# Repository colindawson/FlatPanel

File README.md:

# Remote FlatPanel to help with taking calibration frames.

This flat panel is going to be an open source, dimmable flat panel for astronomy.

## Features
- Dimmable flat panel
- Optional dew heater
- Flat panel acts like lens cap
- AsiAir remote controlable (both for heater and panel)
- oLed display for local control
- Wifi remote control
- Ascom Alpaca control
- Temperature and humidity sensor
- Fully automatic mode for dew heater

Above is the fully list of features that I'm planning.  Some of the features will cancel out other features. For example Fully Automatic mode will be available for the dew heater, to use the minimum power so that it keeps away dew without human interaction, however I want to have the ability to overrride this in several ways - Using an output from the AsiAir, a dedicated web page, Ascom Alpaca or manually via the display.

The plan is that this is going to be a full solution for any size scope, however, my initial project is based on creating a Panel for my SpaceCat 51 Scope.   Once that is working, I'll be looking at how to modify the project to work with my Meade LX-90.

## Discord

[cjdSkunkWorks/FlatPanel](https://discord.com/channels/800391513091211284/1350925191181631498)

## Todo list
- ~~Upload Display board design prototype~~ (done)
- ~~Upload Mainboard design prototype~~ (done)
- Finish designing 3D files for the SpaceCat51
  
- Upload 3d models for the SpaceCat51
- Finalise PCB Layout for Display Board
- Finalise PCB Layout for Mainboard
- Figure out display controls for manual mode
- Create micropython source oode for Pico
- Upgrade MicroPython code to support Pico W, for Web access
- Upgrade MicroPyton code to implement ASCOM Alpaca support

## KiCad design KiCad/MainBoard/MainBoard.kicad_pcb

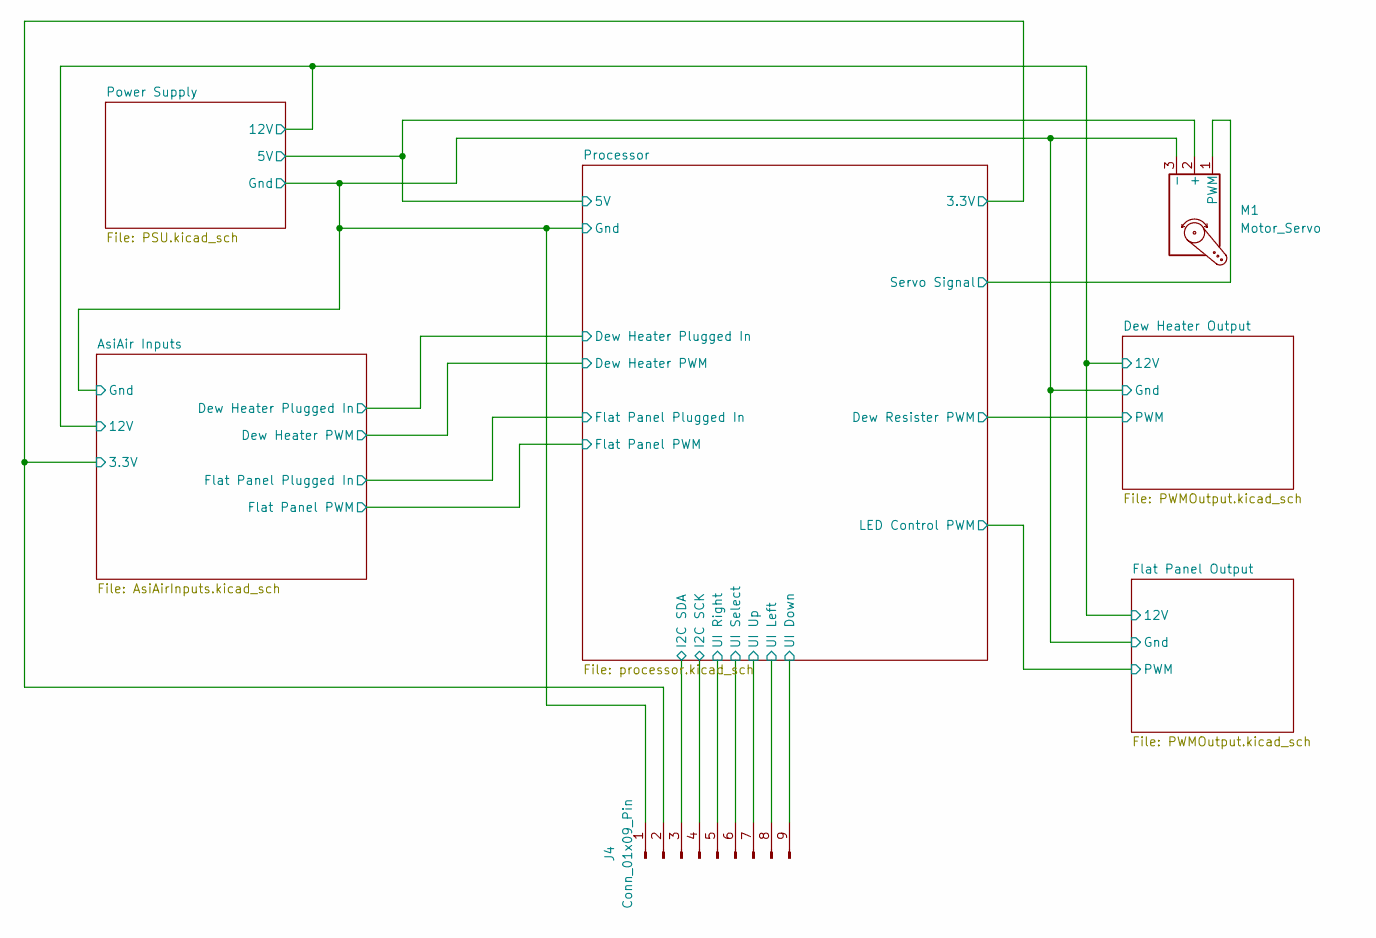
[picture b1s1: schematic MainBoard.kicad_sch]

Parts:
J4: Conn_01x09_Pin; PinHeader_2x05_P2.54mm_Horizontal
M1: Motor_Servo; PinHeader_1x03_P2.54mm_Vertical

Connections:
/AsiAir Inputs/3.3V: J4.2; also elsewhere on the board
/AsiAir Inputs/Gnd: J4.1, M1.3 (-); also elsewhere on the board
/Power Supply/5V: M1.2 (+); also elsewhere on the board
/Processor/I2C SCK: J4.4; also elsewhere on the board
/Processor/I2C SDA: J4.3; also elsewhere on the board
/Processor/Servo Signal: M1.1 (PWM); also elsewhere on the board
/Processor/UI Down: J4.9; also elsewhere on the board
/Processor/UI Left: J4.8; also elsewhere on the board
/Processor/UI Right: J4.5; also elsewhere on the board
/Processor/UI Select: J4.6; also elsewhere on the board
/Processor/UI Up: J4.7; also elsewhere on the board

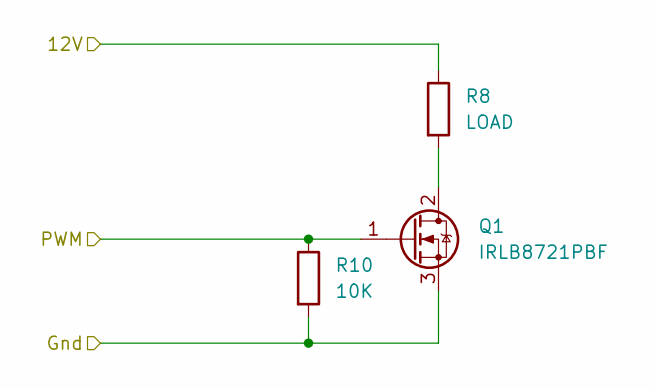
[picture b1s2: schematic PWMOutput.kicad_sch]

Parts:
Q1: IRLB8721PBF; TO-220-3_Vertical
R8: LOAD; JST_XH_B2B-XH-A_1x02_P2.50mm_Vertical
R10: 10K; R_Axial_DIN0204_L3.6mm_D1.6mm_P5.08mm_Horizontal

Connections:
/AsiAir Inputs/12V: R8.1; also elsewhere on the board
/AsiAir Inputs/Gnd: Q1.3 (S), R10.2; also elsewhere on the board
/Dew Heater Output/PWM: Q1.1 (G), R10.1; also elsewhere on the board
unnamed: Q1.2 (D), R8.2

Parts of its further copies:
Q2: IRLB8721PBF; TO-220-3_Vertical
R9: LOAD; JST_XH_B2B-XH-A_1x02_P2.50mm_Vertical
R11: 10K; R_Axial_DIN0204_L3.6mm_D1.6mm_P5.08mm_Horizontal

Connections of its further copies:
/AsiAir Inputs/12V: R9.1; also elsewhere on the board
/AsiAir Inputs/Gnd: Q2.3 (S), R11.2; also elsewhere on the board
/Flat Panel Output/PWM: Q2.1 (G), R11.1; also elsewhere on the board
unnamed: Q2.2 (D), R9.2

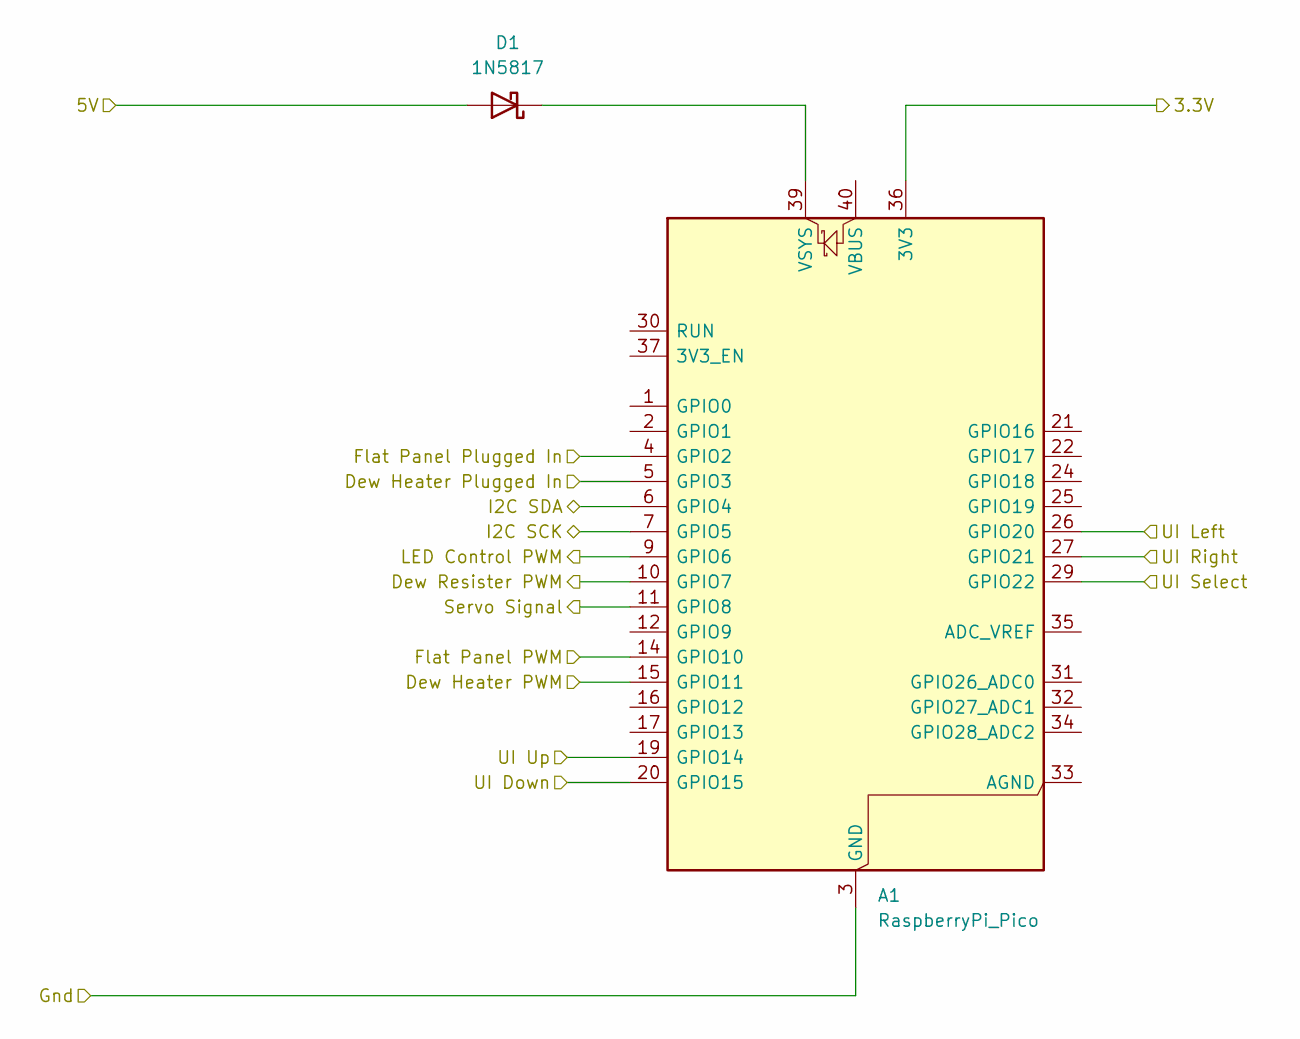
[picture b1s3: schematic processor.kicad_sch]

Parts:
A1: RaspberryPi_Pico; RaspberryPi_Pico_Common_Unspecified
D1: 1N5817; D_DO-15_P10.16mm_Horizontal

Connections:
/AsiAir Inputs/3.3V: A1.36 (3V3); also elsewhere on the board
/AsiAir Inputs/Dew Heater PWM: A1.15 (GPIO11); also elsewhere on the board
/AsiAir Inputs/Dew Heater Plugged In: A1.5 (GPIO3); also elsewhere on the board
/AsiAir Inputs/Flat Panel PWM: A1.14 (GPIO10); also elsewhere on the board
/AsiAir Inputs/Flat Panel Plugged In: A1.4 (GPIO2); also elsewhere on the board
/AsiAir Inputs/Gnd: A1.3 (GND), A1.8 (GND), A1.13 (GND), A1.18 (GND), A1.23 (GND), A1.28 (GND), A1.38 (GND); also elsewhere on the board
/Dew Heater Output/PWM: A1.10 (GPIO7); also elsewhere on the board
/Flat Panel Output/PWM: A1.9 (GPIO6); also elsewhere on the board
/Power Supply/5V: D1.2 (A); also elsewhere on the board
/Processor/I2C SCK: A1.7 (GPIO5); also elsewhere on the board
/Processor/I2C SDA: A1.6 (GPIO4); also elsewhere on the board
/Processor/Servo Signal: A1.11 (GPIO8); also elsewhere on the board
/Processor/UI Down: A1.20 (GPIO15); also elsewhere on the board
/Processor/UI Left: A1.26 (GPIO20); also elsewhere on the board
/Processor/UI Right: A1.27 (GPIO21); also elsewhere on the board
/Processor/UI Select: A1.29 (GPIO22); also elsewhere on the board
/Processor/UI Up: A1.19 (GPIO14); also elsewhere on the board
unnamed: A1.39 (VSYS), D1.1 (K)

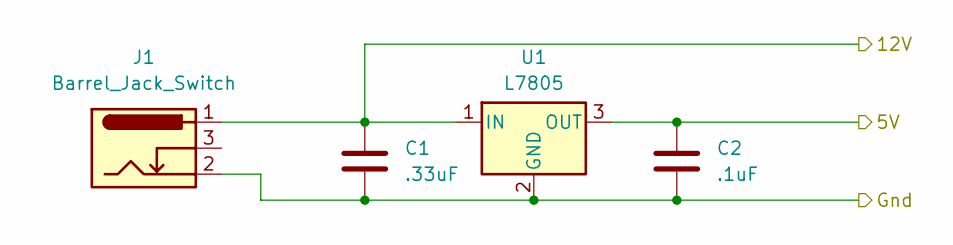
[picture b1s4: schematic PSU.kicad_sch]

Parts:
C1: .33uF; C_Disc_D5.0mm_W2.5mm_P5.00mm
C2: .1uF; C_Disc_D5.0mm_W2.5mm_P5.00mm
J1: Barrel_Jack_Switch; BarrelJack_Horizontal
U1: L7805; TO-220-3_Vertical

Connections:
/AsiAir Inputs/12V: C1.1, J1.1, U1.1 (IN); also elsewhere on the board
/AsiAir Inputs/Gnd: C1.2, C2.2, J1.2, U1.2 (GND); also elsewhere on the board
/Power Supply/5V: C2.1, U1.3 (OUT); also elsewhere on the board

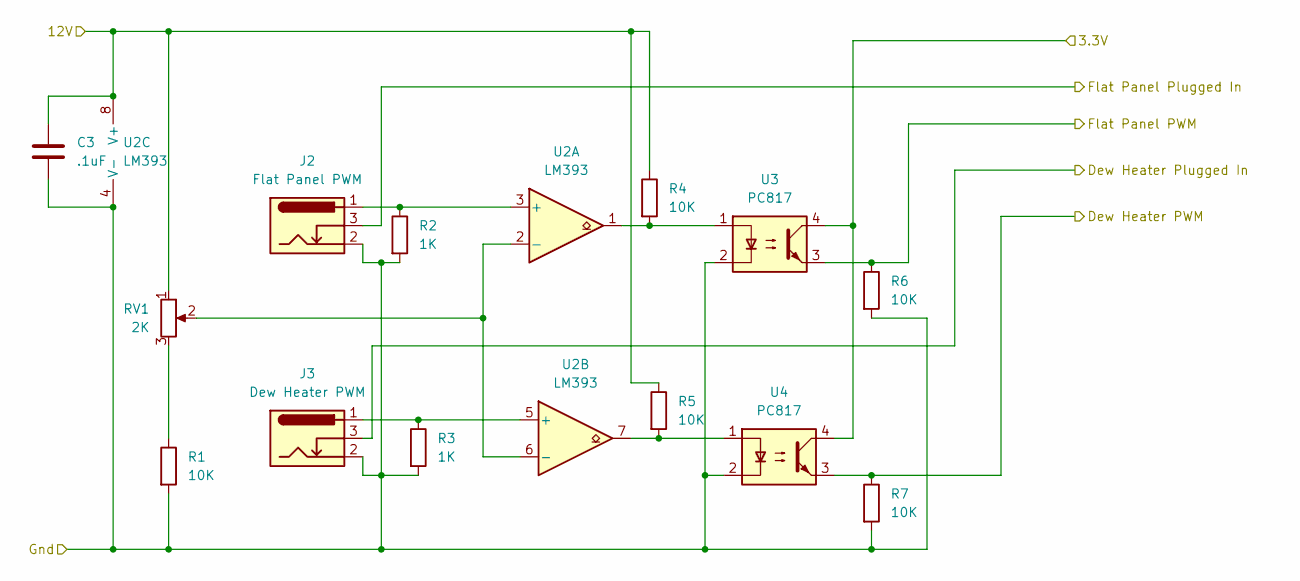
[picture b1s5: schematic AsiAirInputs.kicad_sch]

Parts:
C3: .1uF; C_Disc_D5.0mm_W2.5mm_P5.00mm
J2: Flat Panel PWM; BarrelJack_Horizontal
J3: Dew Heater PWM; BarrelJack_Horizontal
R1, R4, R5, R6, R7: 10K; R_Axial_DIN0204_L3.6mm_D1.6mm_P5.08mm_Horizontal
R2, R3: 1K; R_Axial_DIN0204_L3.6mm_D1.6mm_P5.08mm_Horizontal
RV1: 2K; Potentiometer_Runtron_RM-065_Vertical
U2: LM393; DIP-8_W7.62mm_Socket
U3, U4: PC817; DIP-4_W7.62mm

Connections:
/AsiAir Inputs/3.3V: U3.4, U4.4; also elsewhere on the board
/AsiAir Inputs/12V: C3.1, R4.1, R5.1, RV1.1, U2.8 (V+); also elsewhere on the board
/AsiAir Inputs/Dew Heater PWM: R7.1, U4.3; also elsewhere on the board
/AsiAir Inputs/Dew Heater Plugged In: J3.3; also elsewhere on the board
/AsiAir Inputs/Flat Panel PWM: R6.1, U3.3; also elsewhere on the board
/AsiAir Inputs/Flat Panel Plugged In: J2.3; also elsewhere on the board
/AsiAir Inputs/Gnd: C3.2, J2.2, J3.2, R1.2, R2.2, R3.2, R6.2, R7.2, U2.4 (V-), U3.2, U4.2; also elsewhere on the board
unnamed: R1.1, RV1.3
unnamed: R4.2, U2.1, U3.1
unnamed: R5.2, U2.7, U4.1
unnamed: J2.1, R2.1, U2.3 (+)
unnamed: RV1.2, U2.2 (-), U2.6 (-)
unnamed: J3.1, R3.1, U2.5 (+)

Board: 2 copper layers, 28 parts (0 on the bottom side), 27 nets, no tracks yet.

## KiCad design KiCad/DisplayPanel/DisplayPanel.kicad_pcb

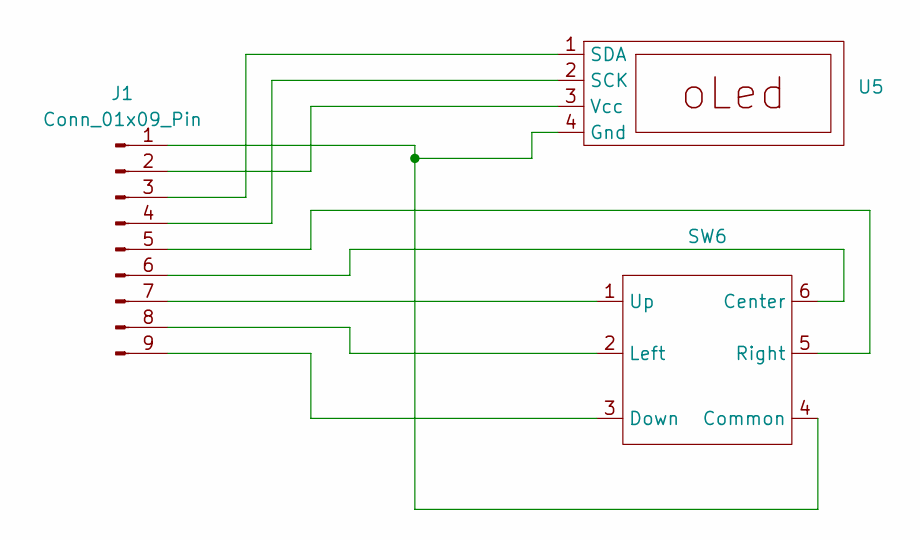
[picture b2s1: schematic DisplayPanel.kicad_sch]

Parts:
J1: Conn_01x09_Pin; PinHeader_2x05_P2.54mm_Horizontal
SW6: 5WayNavigationSwitch
U5: PinHeader_1x04_P2.54mm_Vertical

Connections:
unnamed: J1.1, SW6.4 (Common), U5.4 (Gnd)
unnamed: J1.2, U5.3 (Vcc)
unnamed: J1.3, U5.1 (SDA)
unnamed: J1.4, U5.2 (SCK)
unnamed: J1.5, SW6.5 (Right)
unnamed: J1.6, SW6.6 (Center)
unnamed: J1.7, SW6.1 (Up)
unnamed: J1.8, SW6.2 (Left)
unnamed: J1.9, SW6.3 (Down)

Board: 2 copper layers, 3 parts (0 on the bottom side), 9 nets, no tracks yet.

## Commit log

2025-03-14 Adding prototype for the display panel circuit
2025-03-14 Adding prototype for the Mainboard
2025-03-14 Added the current test program for the Pico
2025-03-16 3d Model work in progress
